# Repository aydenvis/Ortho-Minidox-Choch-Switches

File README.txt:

Rev1 is the Ortho one, Rev2 is the columnar staggered one. Rev3 is the hotswap one.
Any questions, PM Quiz#5800

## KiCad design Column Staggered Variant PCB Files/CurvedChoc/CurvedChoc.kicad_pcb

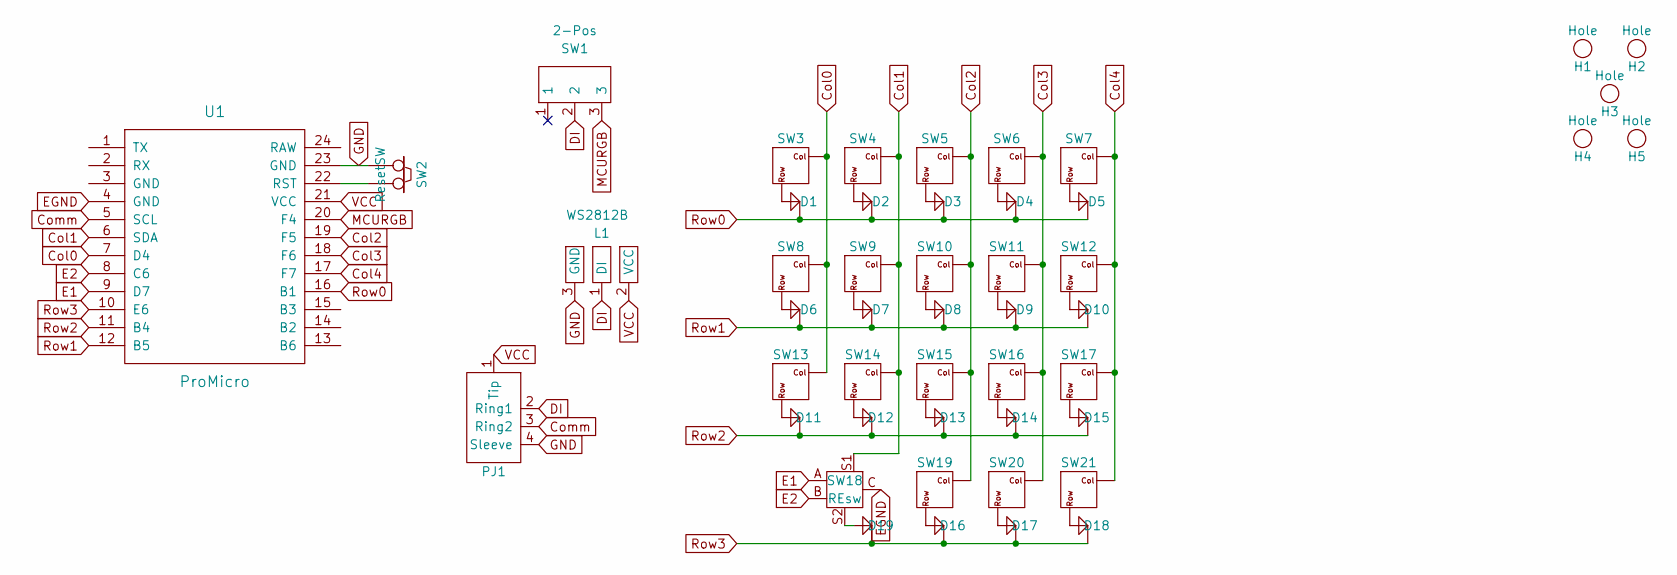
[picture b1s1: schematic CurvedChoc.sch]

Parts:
D1, D2, D3, D4, D5, D6, D7, D8, D9, D10, D11, D12, D13, D14, D15, D16, D17, D18, D19: Diode
H1, H2, H3, H4, H5: Hole; Hole_2mm
L1: WS2812B; WS2812B-Pad
PJ1: PJ-320A; TRRS-PJ-320A-dual
SW1: 2-Pos; 2Pos-Switch
SW2: ResetSW
SW3, SW4, SW5, SW6, SW7, SW8, SW9, SW10, SW11, SW12, SW13, SW14, SW15, SW16, SW17, SW19, SW20, SW21: Switch; MX_Choc_Symmetric
SW18: REsw
U1: ProMicro

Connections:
Col0: SW3.1, SW8.1, SW13.1, U1.7 (D4)
Col1: SW4.1, SW9.1, SW14.1, SW18.S1, U1.6 (SDA)
Col2: SW5.1, SW10.1, SW15.1, SW19.1, U1.19 (F5)
Col3: SW6.1, SW11.1, SW16.1, SW20.1, U1.18 (F6)
Col4: SW7.1, SW12.1, SW17.1, SW21.1, U1.17 (F7)
Comm: PJ1.3 (Ring2), U1.5 (SCL)
DI: L1.1 (DI), PJ1.2 (Ring1), SW1.2
E1: SW18.A, U1.9 (D7)
E2: SW18.B, U1.8 (C6)
EGND: SW18.C, U1.4 (GND)
GND: L1.3 (GND), PJ1.4 (Sleeve), SW2.1, U1.23 (GND)
MCURGB: SW1.3, U1.20 (F4)
unnamed: D1.1 (K), SW3.2
unnamed: D2.1 (K), SW4.2
unnamed: D3.1 (K), SW5.2
unnamed: D4.1 (K), SW6.2
unnamed: D5.1 (K), SW7.2
unnamed: D6.1 (K), SW8.2
unnamed: D7.1 (K), SW9.2
unnamed: D8.1 (K), SW10.2
unnamed: D9.1 (K), SW11.2
unnamed: D10.1 (K), SW12.2
unnamed: D11.1 (K), SW13.2
unnamed: D12.1 (K), SW14.2
unnamed: D13.1 (K), SW15.2
unnamed: D14.1 (K), SW16.2
unnamed: D15.1 (K), SW17.2
unnamed: D16.1 (K), SW19.2
unnamed: D17.1 (K), SW20.2
unnamed: D18.1 (K), SW21.2
unnamed: D19.1 (K), SW18.S2
unnamed: SW2.2, U1.22 (RST)
Row0: D1.2 (A), D2.2 (A), D3.2 (A), D4.2 (A), D5.2 (A), U1.16 (B1)
Row1: D6.2 (A), D7.2 (A), D8.2 (A), D9.2 (A), D10.2 (A), U1.12 (B5)
Row2: D11.2 (A), D12.2 (A), D13.2 (A), D14.2 (A), D15.2 (A), U1.11 (B4)
Row3: D16.2 (A), D17.2 (A), D18.2 (A), D19.2 (A), U1.10 (E6)
VCC: L1.2 (VCC), PJ1.1 (Tip), U1.21 (VCC)

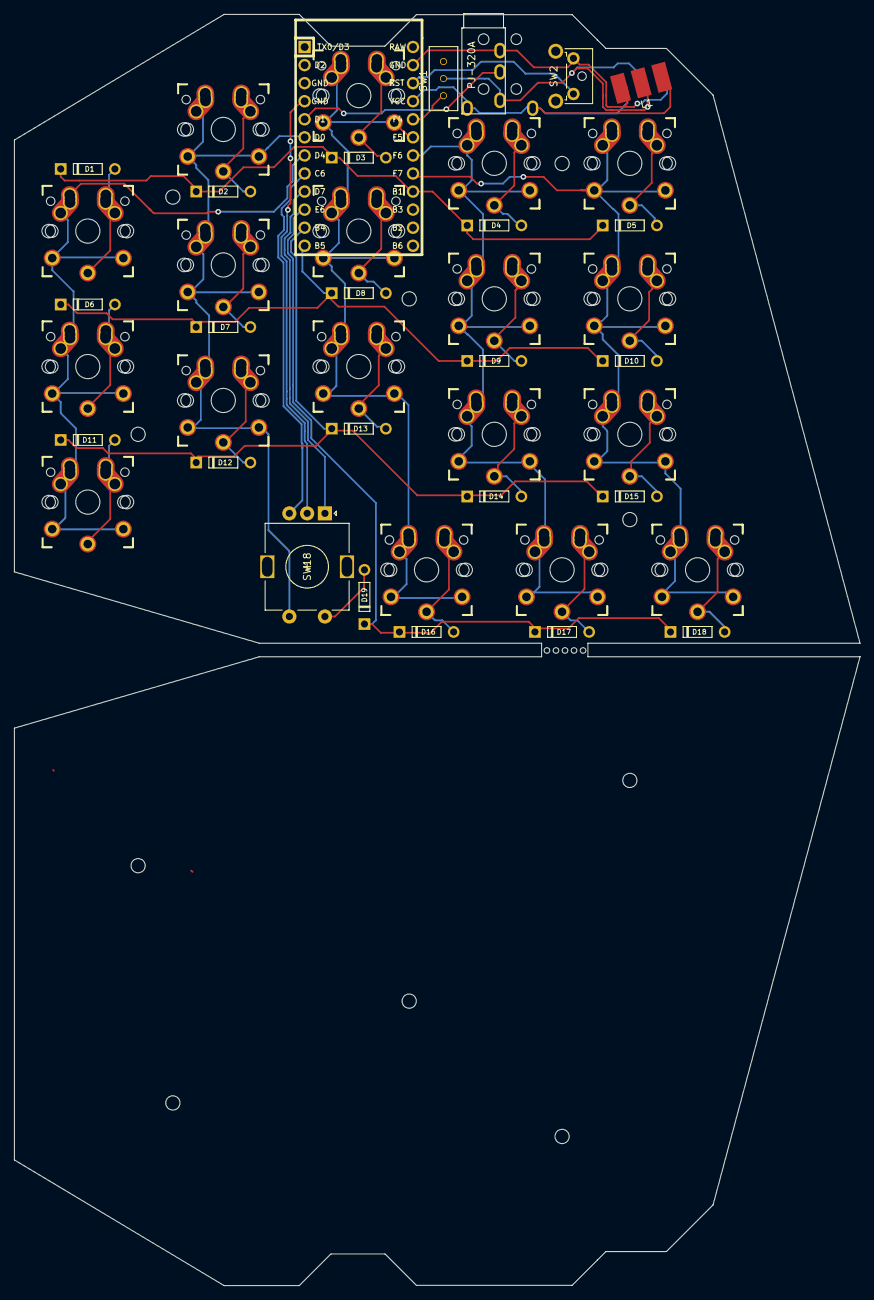
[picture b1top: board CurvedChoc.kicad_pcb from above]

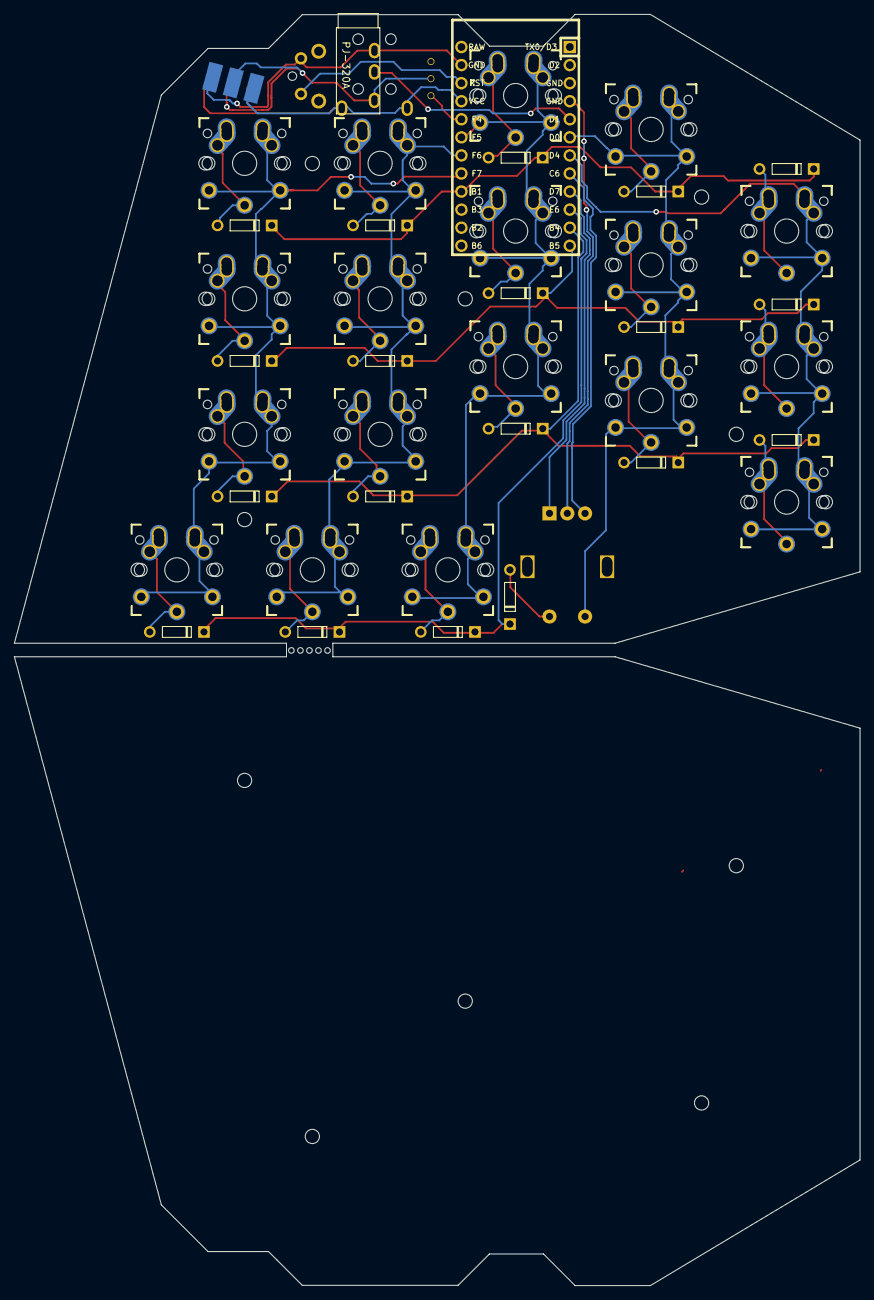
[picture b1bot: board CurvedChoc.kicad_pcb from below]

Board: 2 copper layers, 118.9 x 178.7 mm, 53 parts (5 on the bottom side), 37 nets.

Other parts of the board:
H1#2, H2#2, H3#2, H4#2, H5#2: Hole; Hole_2mm

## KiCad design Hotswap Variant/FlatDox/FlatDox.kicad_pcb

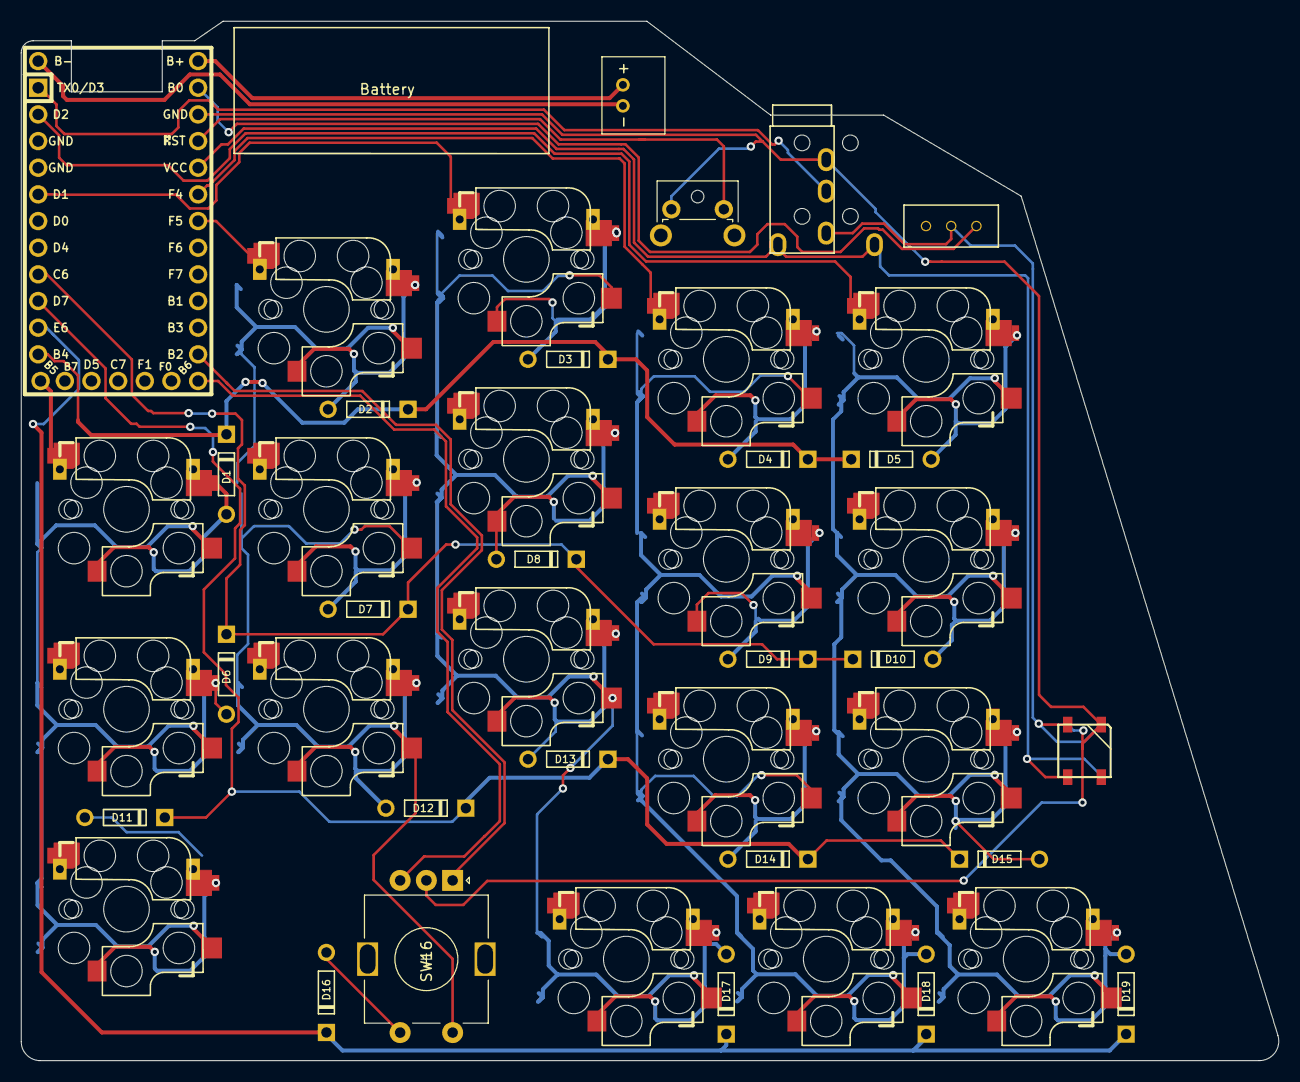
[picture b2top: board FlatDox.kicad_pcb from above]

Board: 2 copper layers, 119.8 x 99.0 mm, 45 parts (1 on the bottom side), 38 nets.

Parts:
C1: 2PIN_JST; 2Pin_JST
D1, D2, D3, D4, D5, D6, D7, D8, D9, D10, D11, D12, D13, D14, D15, D16, D17, D18, D19: Diode
L1, L2: WS2812B_Single; WS2812B
PJ1: PJ-320A; TRRS-PJ-320A-dual
SW1, SW2, SW3, SW4, SW5, SW6, SW7, SW8, SW9, SW10, SW11, SW12, SW13, SW14, SW15, SW17, SW18, SW19: Switch; MX_Choc_Symmetric_HotSwap
SW16: Rotary_Encoder_w_Switch; Rotary_Encoder_with_Switch
SW20: 2-Pos; 2Pos-Switch
SW21: ResetSW
U1: Elite-C

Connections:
COMM: PJ1.3, U1.1
Col0: SW1.1, SW6.1, SW11.1, U1.12
Col1: SW2.1, SW7.1, SW12.1, SW16.S2, U1.19
Col2: SW3.1, SW8.1, SW13.1, SW17.1, U1.5
Col3: SW4.1, SW9.1, SW14.1, SW18.1, U1.20
Col4: SW5.1, SW10.1, SW15.1, SW19.1, U1.2
DI: L1.4, L2.4, PJ1.2, SW20.2
E1: SW16.A, U1.14
E2: SW16.B, U1.13
Gnd: L1.3, L2.3, PJ1.4, SW16.C, SW21.1, U1.23
MCURGB: SW20.3, U1.24
unnamed: C1.1, U1.31
unnamed: C1.2, U1.30
unnamed: D1.1, SW1.2
unnamed: D2.1, SW2.2
unnamed: D3.1, SW3.2
unnamed: D4.1, SW4.2
unnamed: D5.1, SW5.2
unnamed: D6.1, SW6.2
unnamed: D7.1, SW7.2
unnamed: D8.1, SW8.2
unnamed: D9.1, SW9.2
unnamed: D10.1, SW10.2
unnamed: D11.1, SW11.2
unnamed: D12.1, SW12.2
unnamed: D13.1, SW13.2
unnamed: D14.1, SW14.2
unnamed: D15.1, SW15.2
unnamed: D16.1, SW16.S1
unnamed: D17.1, SW17.2
unnamed: D18.1, SW18.2
unnamed: D19.1, SW19.2
unnamed: SW21.2, U1.22
Row0: D1.2, D2.2, D3.2, D4.2, D5.2, U1.11
Row1: D6.2, D7.2, D8.2, D9.2, D10.2, U1.8
Row2: D11.2, D12.2, D13.2, D14.2, D15.2, U1.9
Row3: D16.2, D17.2, D18.2, D19.2, U1.10
VCC: L1.1, L2.1, PJ1.1, U1.21

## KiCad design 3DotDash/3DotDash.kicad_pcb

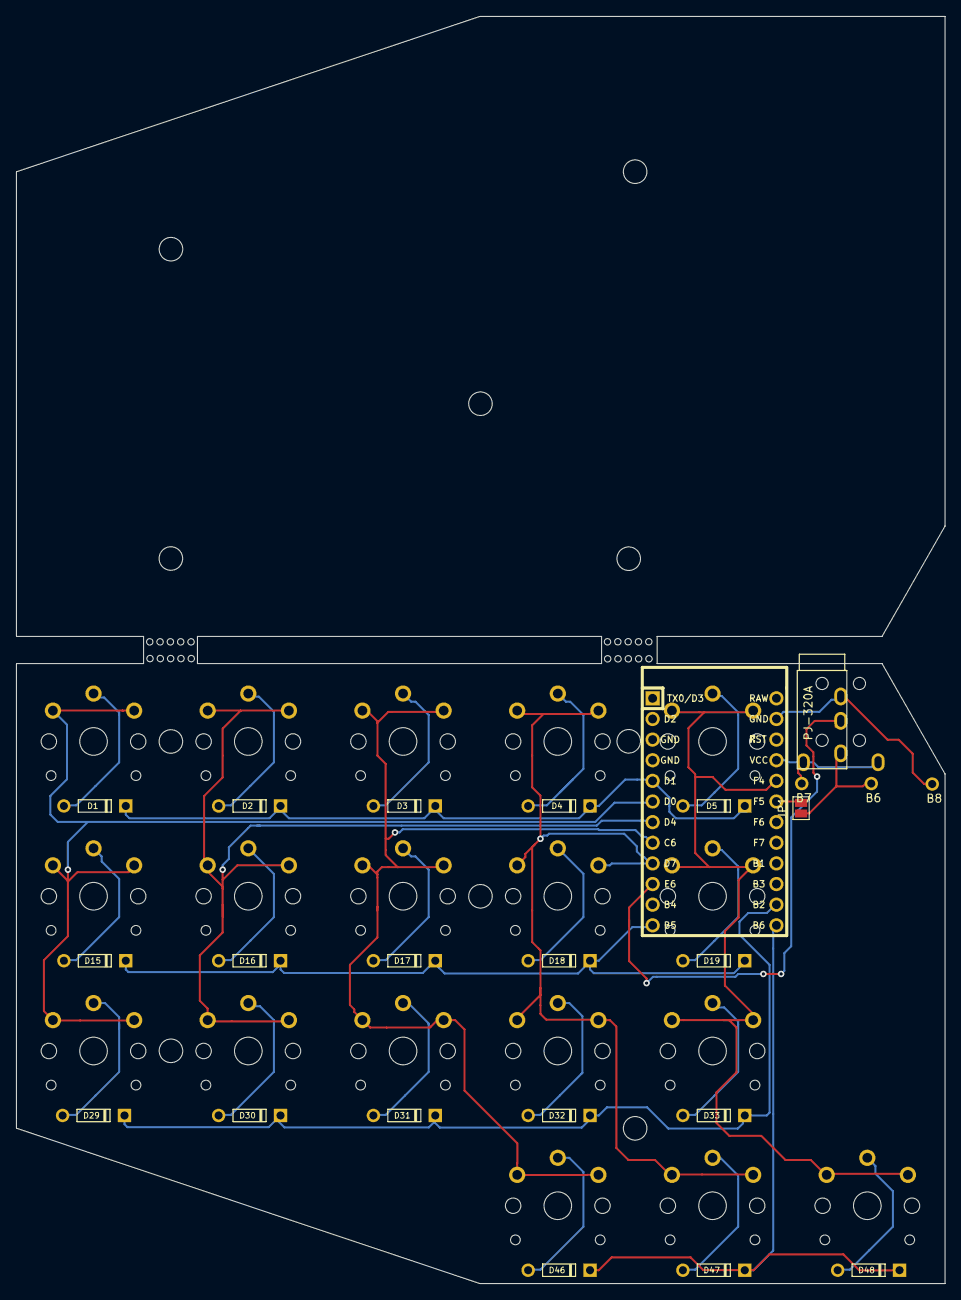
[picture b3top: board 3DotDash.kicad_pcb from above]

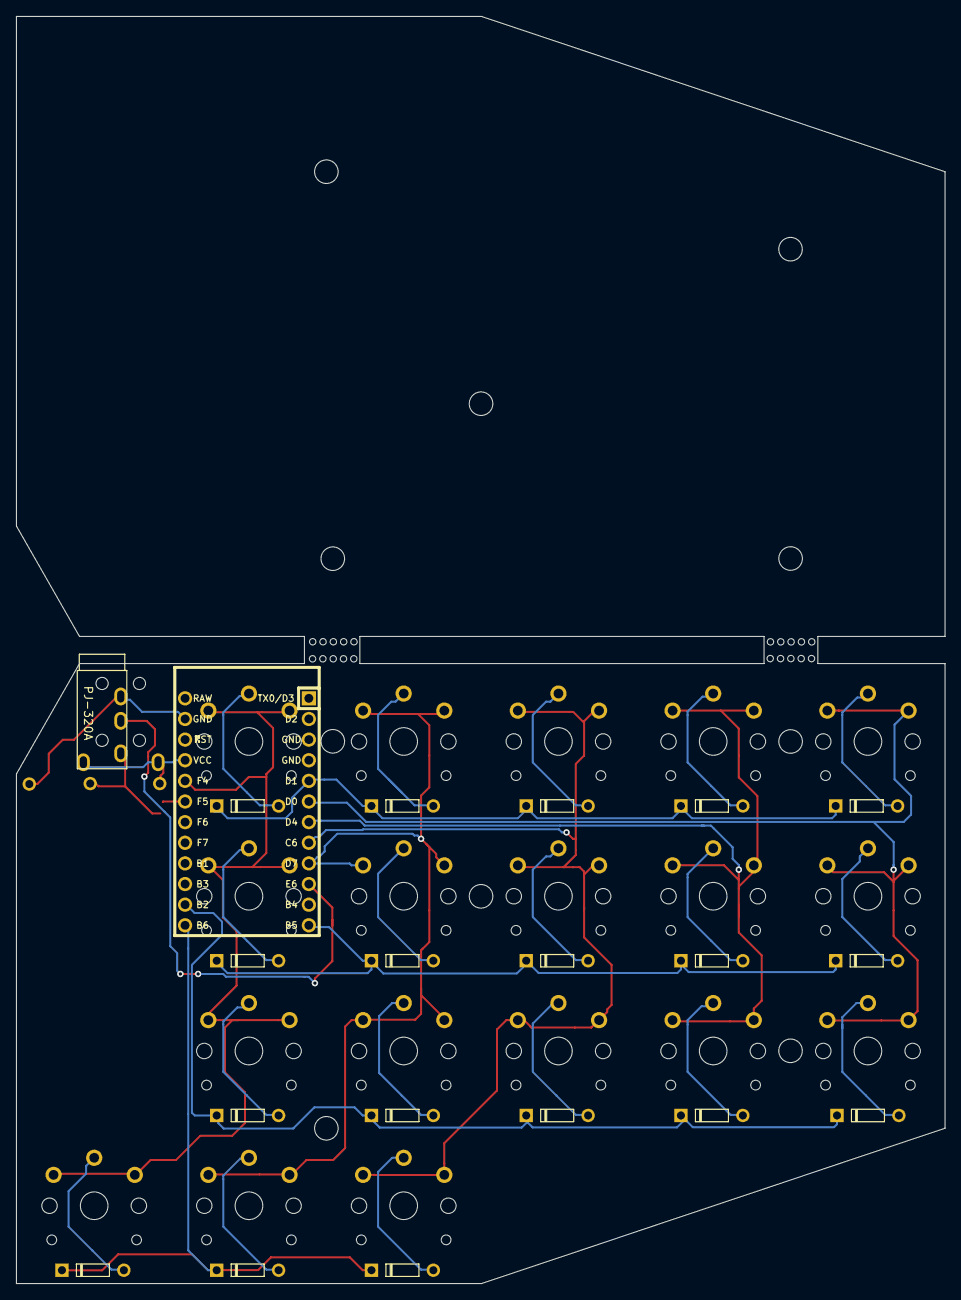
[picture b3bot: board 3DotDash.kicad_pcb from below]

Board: 2 copper layers, 114.3 x 156.0 mm, 52 parts (5 on the bottom side), 32 nets.

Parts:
B1, B1#2, B2, B2#2, B3, B3#2, B4, B4#2, B5, B5#2: Breakout; MountingHole_2.9mm
B6, B7, B8: Breakout
D1, D2, D3, D4, D5, D15, D16, D17, D18, D19, D29, D30, D31, D32, D33, D46, D47, D48: Diode
JP1: Jumper; SolderJumper
PJ1: PJ-320A; TRRS-PJ-320A-dual
SW1, SW2, SW3, SW4, SW5, SW15, SW16, SW17, SW18, SW19, SW29, SW30, SW31, SW32, SW33, SW46, SW47, SW48: Switch; KailhChoc-1U
U1: ProMicro; ArduinoProMicro

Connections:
COMMGnd: B8.1, PJ1.4, U1.23
COMMVcc: B7.1, PJ1.1, U1.21
Col0: SW1.1, SW15.1, SW29.1, U1.6
Col1: SW2.1, SW16.1, SW30.1, U1.7
Col2: SW3.1, SW17.1, SW31.1, SW46.1, U1.8
Col3: SW4.1, SW18.1, SW32.1, SW47.1, U1.9
Col4: SW5.1, SW19.1, SW33.1, SW48.1, U1.20
Comm: PJ1.3, U1.10
unnamed: B6.1, JP1.2, PJ1.2
unnamed: D1.1, SW1.2
unnamed: D2.1, SW2.2
unnamed: D3.1, SW3.2
unnamed: D4.1, SW4.2
unnamed: D5.1, SW5.2
unnamed: D15.1, SW15.2
unnamed: D16.1, SW16.2
unnamed: D17.1, SW17.2
unnamed: D18.1, SW18.2
unnamed: D19.1, SW19.2
unnamed: D29.1, SW29.2
unnamed: D30.1, SW30.2
unnamed: D31.1, SW31.2
unnamed: D32.1, SW32.2
unnamed: D33.1, SW33.2
unnamed: D46.1, SW46.2
unnamed: D47.1, SW47.2
unnamed: D48.1, SW48.2
RGBJumper: JP1.1, U1.19
Row0: D1.2, D2.2, D3.2, D4.2, D5.2, U1.5
Row1: D15.2, D16.2, D17.2, D18.2, D19.2, U1.12
Row2: D29.2, D30.2, D31.2, D32.2, D33.2, U1.14
Row3: D46.2, D47.2, D48.2, U1.13

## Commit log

2020-06-20 Added all the files
2020-06-20 Added a variant col stagger
2020-09-13 Updated to include Rev2 QMK and Gerbers
2021-03-02 Updated 3/02/21
2021-05-04 No idea
2021-06-24 Added the Flat/Hot dox
2021-07-05 Added default Chocdox hex
2021-07-17 Added Rev3 QMK. Updated file structure. Added Rev2+3 hexfiles
